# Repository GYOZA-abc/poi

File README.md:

# Kumokogi
歩行型VRデバイス「くもこぎ」の基板・ソフト関連のデータ

詳細はこちら
https://bbs.avalontech.jp/t/topic/1225

# License

Softwares is under MIT license

Hardwares is under CC4.0 BY NC

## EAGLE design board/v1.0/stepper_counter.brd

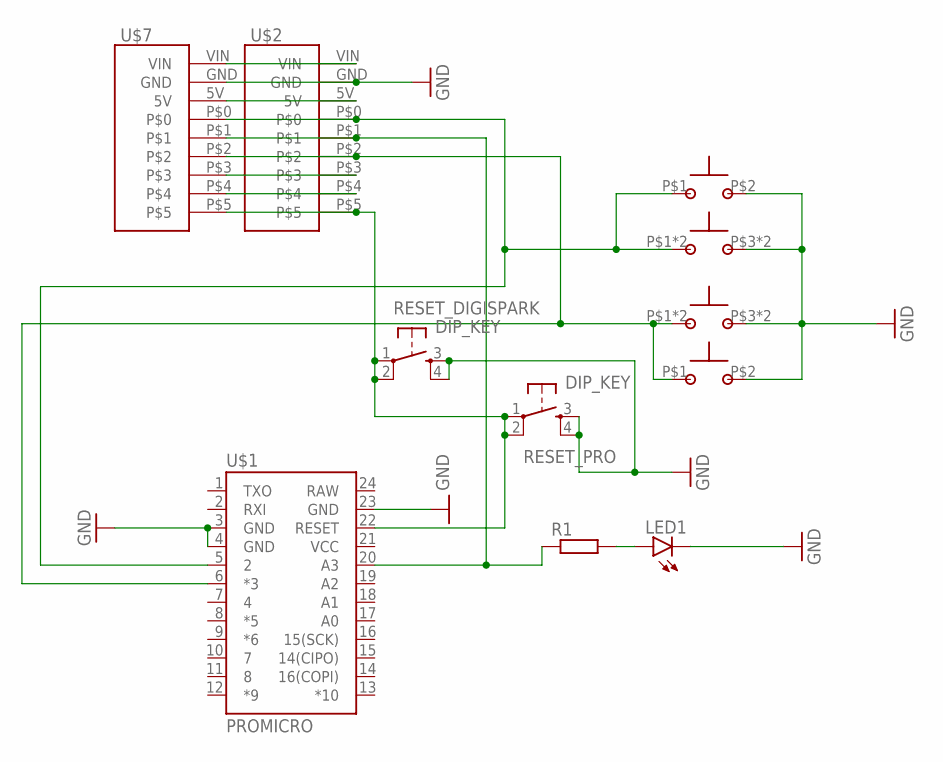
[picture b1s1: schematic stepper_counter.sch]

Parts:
LED1: LED3MM
R1: R-EU_0207/10; 0207/10
RESET_DIGISPARK: DIP_KEY; B3F-10XX
RESET_PRO: DIP_KEY; B3F-10XX
U$1: PROMICRO; SPARKFUN_PRO_MICRO
U$2: DIGISPARK
U$3, U$4: RBS040210
U$5, U$6: SW20D
U$7: DIGISPARK_USB

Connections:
GND: LED1.K (C), RESET_DIGISPARK.3 (S), RESET_DIGISPARK.4 (S1), RESET_PRO.3 (S), RESET_PRO.4 (S1), U$1.3 (GND), U$1.4 (GND), U$1.23 (GND), U$2.GND, U$3.P$3, U$3.P$4, U$4.P$3, U$4.P$4, U$5.P$2, U$6.P$2, U$7.GND
unnamed: R1.1, U$1.20 (A3), U$2.P$1, U$7.P$1
unnamed: LED1.A, R1.2
unnamed: RESET_DIGISPARK.1, RESET_DIGISPARK.2 (P1), RESET_PRO.1, RESET_PRO.2 (P1), U$1.22 (RESET), U$2.P$5, U$7.P$5
unnamed: U$2.VIN, U$7.VIN
unnamed: U$2.5V, U$7.5V
unnamed: U$2.P$3, U$7.P$3
unnamed: U$1.6 (*3), U$2.P$2, U$4.P$1, U$4.P$2, U$6.P$1, U$7.P$2
unnamed: U$1.5 (2), U$2.P$0, U$3.P$1, U$3.P$2, U$5.P$1, U$7.P$0
unnamed: U$2.P$4, U$7.P$4
RAW: U$1.24 (RAW)
VCC: U$1.21 (VCC)

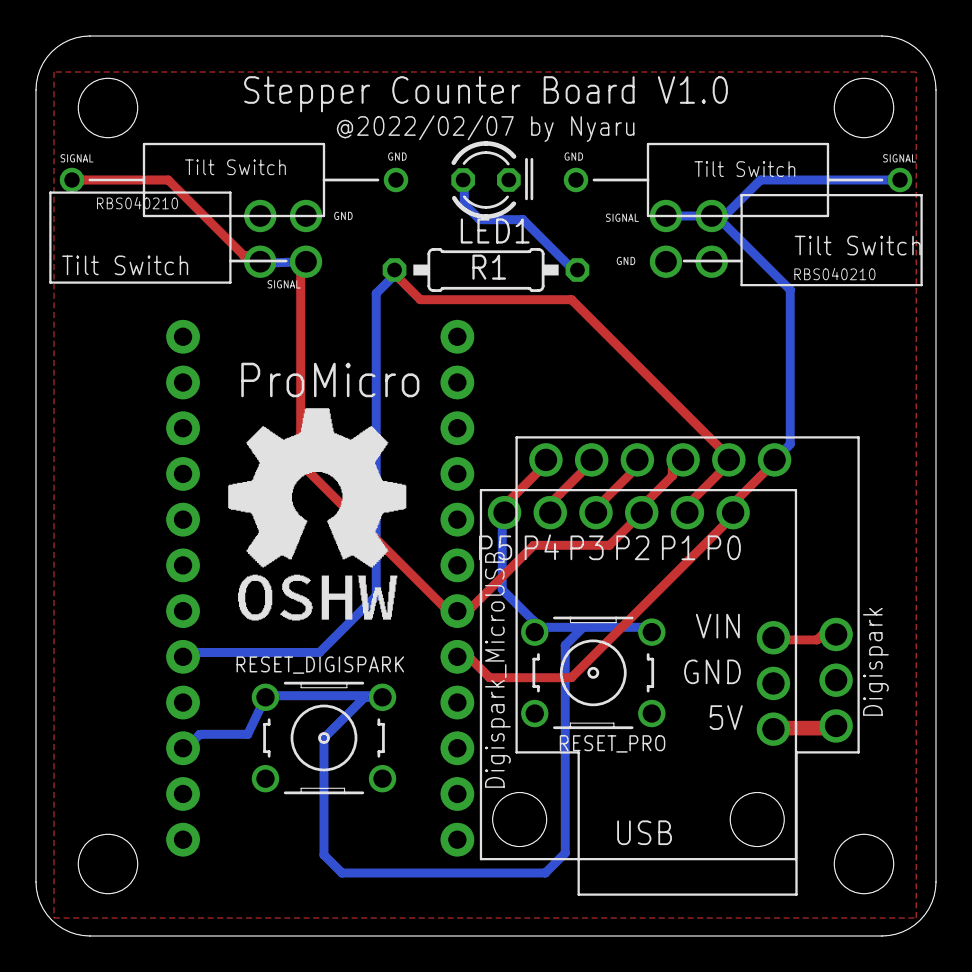
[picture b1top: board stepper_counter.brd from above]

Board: 2 copper layers, 50.0 x 50.0 mm, 11 parts (0 on the bottom side), 10 nets.

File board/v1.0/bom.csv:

Part,Value,Device,Package,Description
LED1,,LED3MM,LED3MM,LED
R1,,R-EU_0207/10,0207/10,RESISTOR
RESET_DIGISPARK,DIP_KEY,DIP_KEY,B3F-10XX,
RESET_PRO,DIP_KEY,DIP_KEY,B3F-10XX,
U$1,PROMICRO,PROMICRO,SPARKFUN_PRO_MICRO,
U$2,DIGISPARK,DIGISPARK,DIGISPARK,
U$3,RBS040210,RBS040210,RBS040210,https://akizukidenshi.com/catalog/g/gP-11714/
U$4,RBS040210,RBS040210,RBS040210,https://akizukidenshi.com/catalog/g/gP-11714/
U$5,SW200D,SW200D,SW200D,
U$6,SW200D,SW200D,SW200D,
U$7,DIGISPARK_USB,DIGISPARK_USB,DIGISPARK_USB,

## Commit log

2022-05-03 add gerber & bom
2022-05-04 Add firmware hex file for digispark
2022-05-04 Create LICENSE
2022-05-04 Add README & digispark upload bat
